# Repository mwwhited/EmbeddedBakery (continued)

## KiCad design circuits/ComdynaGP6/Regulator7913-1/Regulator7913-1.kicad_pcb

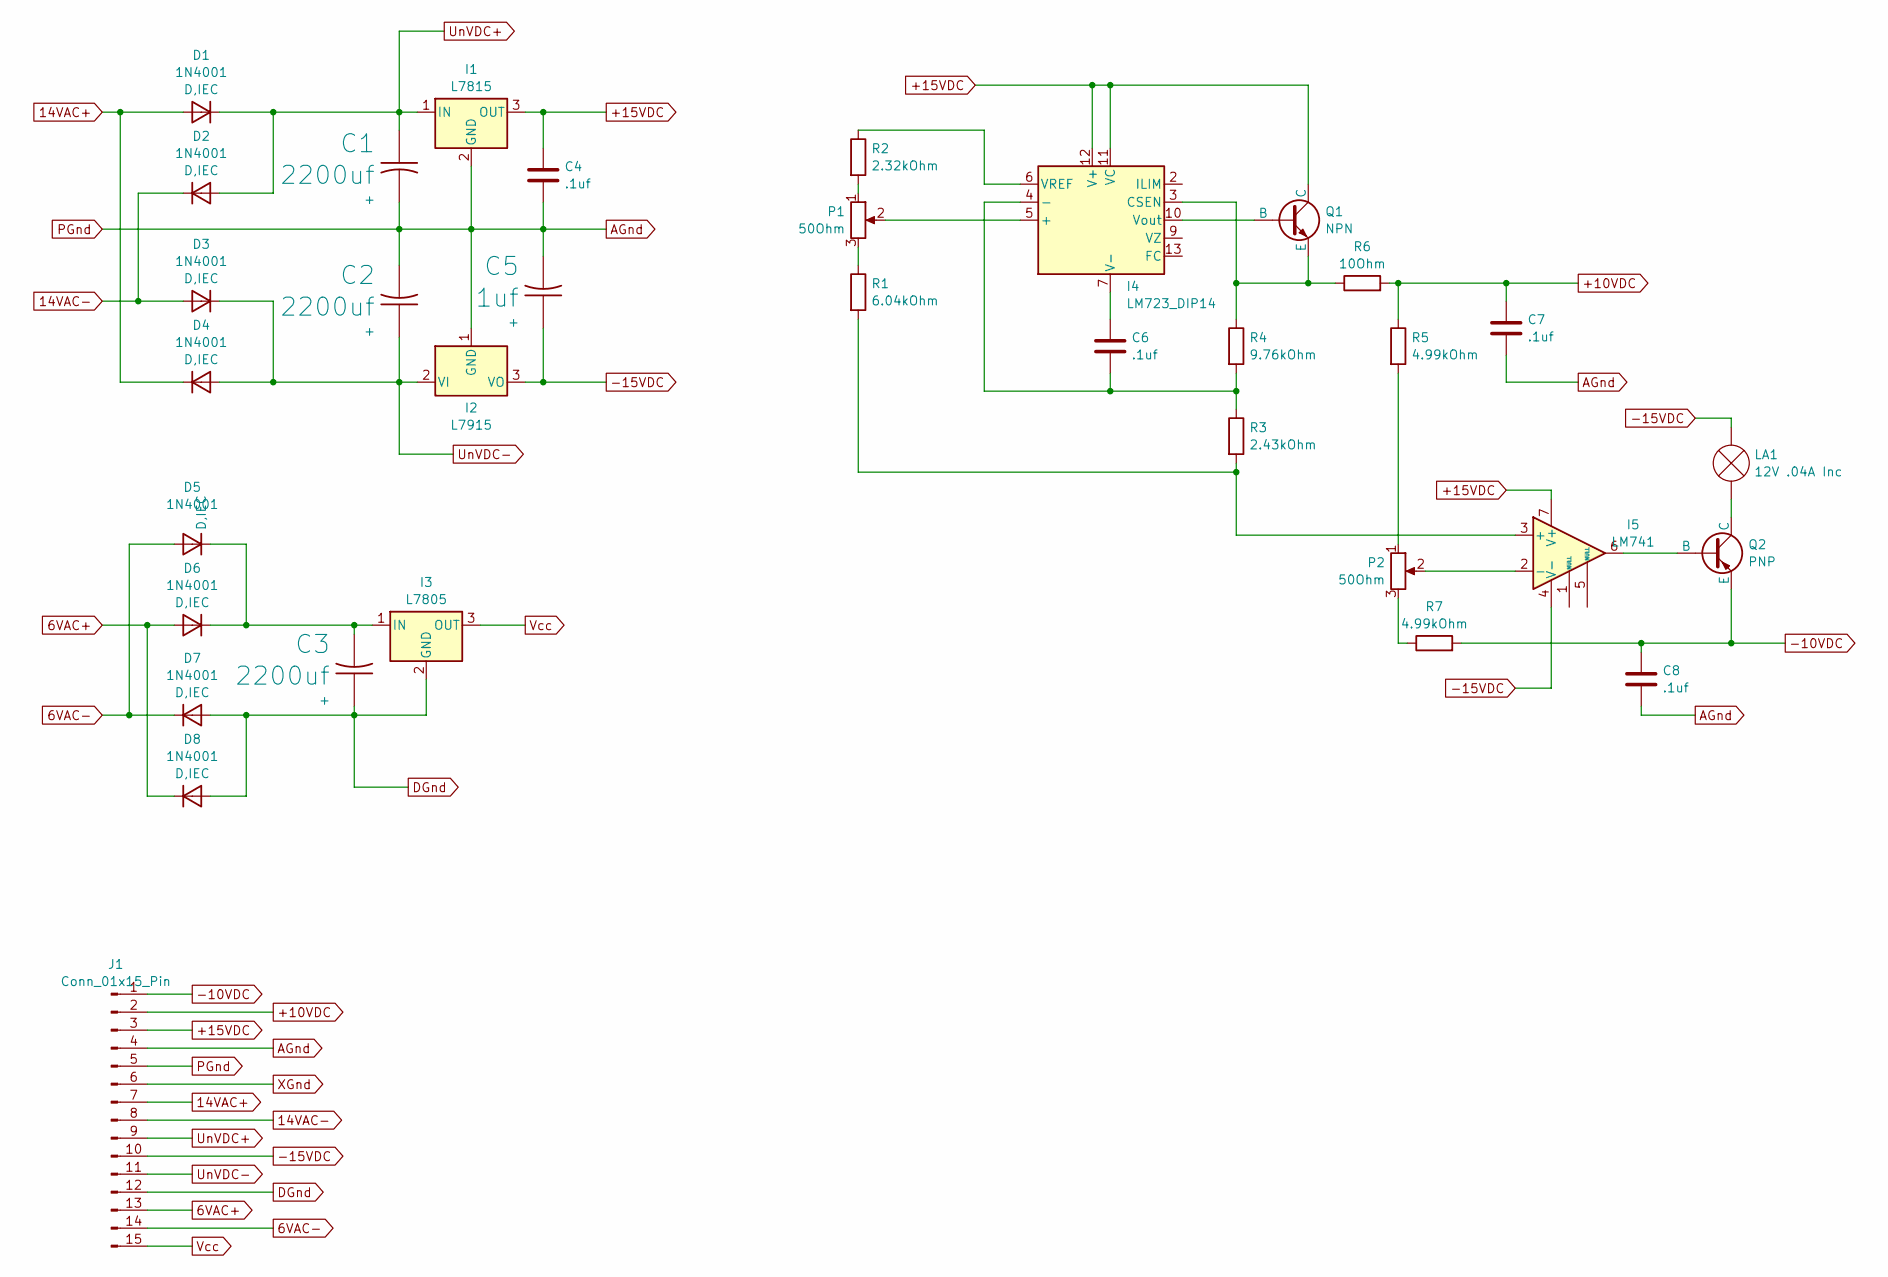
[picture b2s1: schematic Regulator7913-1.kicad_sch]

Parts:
C1, C2, C3: 2200uf; CP_Axial_L30.0mm_D15.0mm_P35.00mm_Horizontal
C4, C6, C7, C8: .1uf; CP_Radial_Tantal_D4.5mm_P5.00mm
C5: 1uf; CP_Radial_Tantal_D4.5mm_P5.00mm
D1, D2, D3, D4, D5, D6, D7, D8: 1N4001; D_5W_P12.70mm_Horizontal
I1: L7815; TO-220-3_Vertical
I2: L7915; TO-220-3_Vertical
I3: L7805; TO-220-3_Vertical
I4: LM723_DIP14; DIP-14_W7.62mm
I5: LM741; DIP-8_W7.62mm_Socket
J1: Conn_01x15_Pin; PinHeader_1x15_P2.54mm_Horizontal
LA1: 12V .04A Inc; PinHeader_1x02_P2.54mm_Horizontal
P1, P2: 50Ohm; Potentiometer_Bourns_3296W_Vertical
Q1: NPN; TO-220-3_Vertical
Q2: PNP; TO-220-3_Vertical
R1: 6.04kOhm; R_Axial_DIN0411_L9.9mm_D3.6mm_P12.70mm_Horizontal
R2: 2.32kOhm; R_Axial_DIN0411_L9.9mm_D3.6mm_P12.70mm_Horizontal
R3: 2.43kOhm; R_Axial_DIN0411_L9.9mm_D3.6mm_P12.70mm_Horizontal
R4: 9.76kOhm; R_Axial_DIN0411_L9.9mm_D3.6mm_P12.70mm_Horizontal
R5, R7: 4.99kOhm; R_Axial_DIN0411_L9.9mm_D3.6mm_P12.70mm_Horizontal
R6: 10Ohm; R_Axial_DIN0411_L9.9mm_D3.6mm_P12.70mm_Horizontal

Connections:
6VAC+: D6.2 (A+), D8.1 (K-), J1.13
6VAC-: D5.2 (A+), D7.1 (K-), J1.14
14VAC+: D1.2 (A+), D4.1 (K-), J1.7
14VAC-: D2.1 (K-), D3.2 (A+), J1.8
+10VDC: C7.1, J1.2, R5.1, R6.2
+15VDC: C4.1, I1.3 (OUT), I4.11 (VC), I4.12 (V+), I5.7 (V+), J1.3, Q1.1 (C)
-10VDC: C8.1, J1.1, Q2.3 (E), R7.2
-15VDC: C5.1 (+), I2.3 (VO), I5.4 (V-), J1.10, LA1.2 (+)
AGnd: C1.2 (-), C2.2 (-), C4.2, C5.2 (-), C7.2, C8.2, I1.2 (GND), I2.1 (GND), J1.4, J1.5
DGnd: C3.1 (+), D7.2 (A+), D8.2 (A+), I3.2 (GND), J1.12
unnamed: C3.2 (-), D5.1 (K-), D6.1 (K-), I3.1 (IN)
unnamed: I4.5 (+), P1.2
unnamed: C6.2, I4.4 (-), R3.1, R4.2
unnamed: I4.3 (CSEN), Q1.3 (E), R4.1, R6.1
unnamed: C6.1, I4.7 (V-)
unnamed: I4.6 (VREF), R2.1
unnamed: I4.10 (Vout), Q1.2 (B)
unnamed: I5.3 (+), R1.2, R3.2
unnamed: I5.2 (-), P2.2
unnamed: LA1.1 (-), Q2.1 (C)
unnamed: P1.1, R2.2
unnamed: P1.3, R1.1
unnamed: P2.1, R5.2
unnamed: P2.3, R7.1
unnamed: I5.6, Q2.2 (B)
UnVDC+: C1.1 (+), D1.1 (K-), D2.2 (A+), I1.1 (IN), J1.9
UnVDC-: C2.1 (+), D3.1 (K-), D4.2 (A+), I2.2 (VI), J1.11
Vcc: I3.3 (OUT), J1.15
XGnd: J1.6

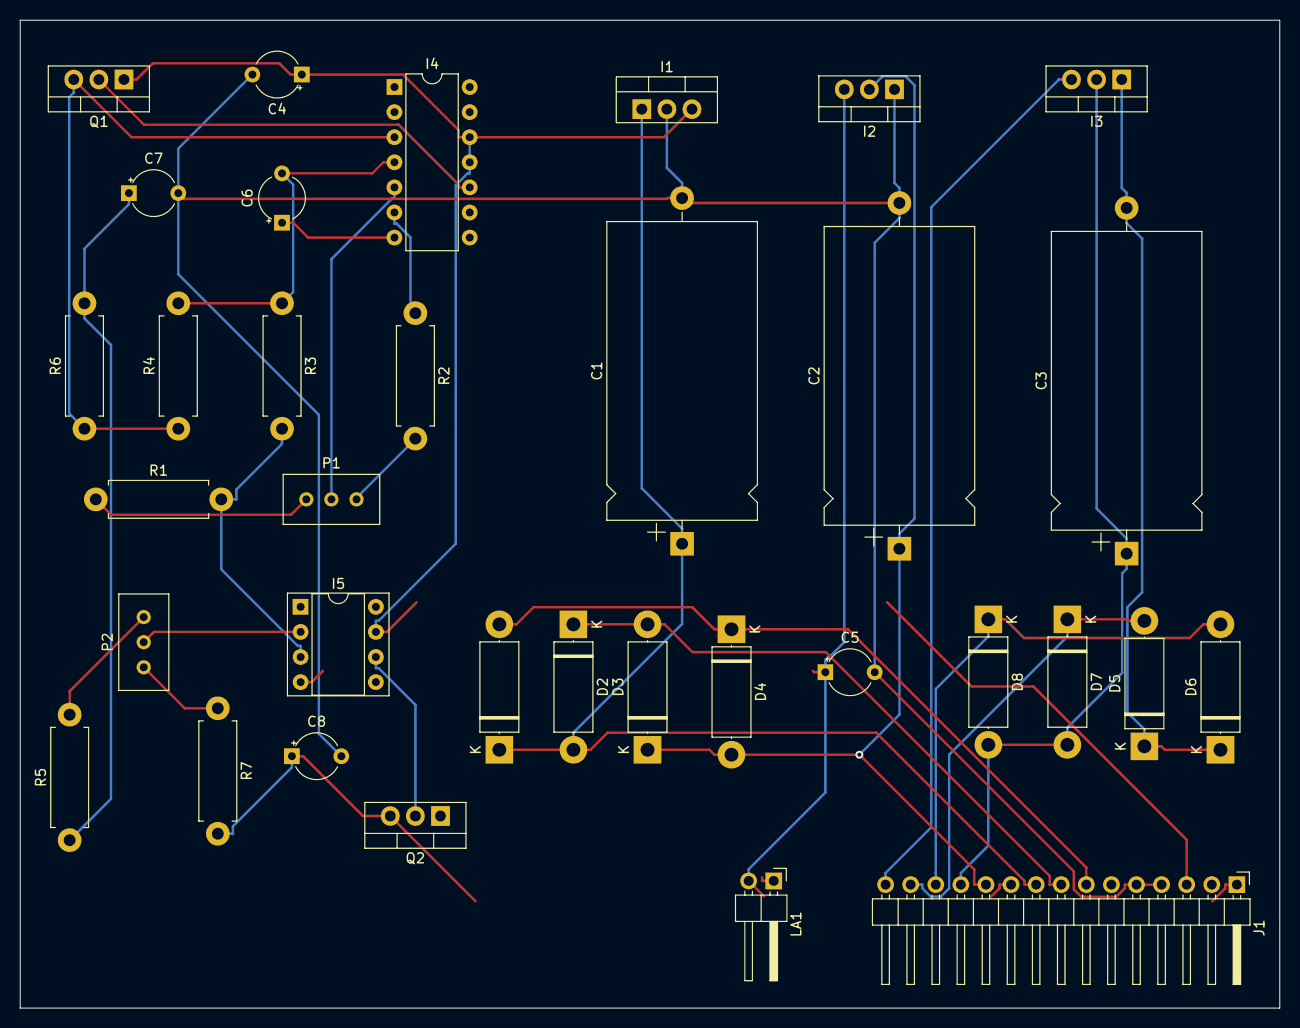
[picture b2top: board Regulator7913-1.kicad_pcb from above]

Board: 2 copper layers, 127.5 x 100.0 mm, 34 parts (0 on the bottom side), 28 nets.

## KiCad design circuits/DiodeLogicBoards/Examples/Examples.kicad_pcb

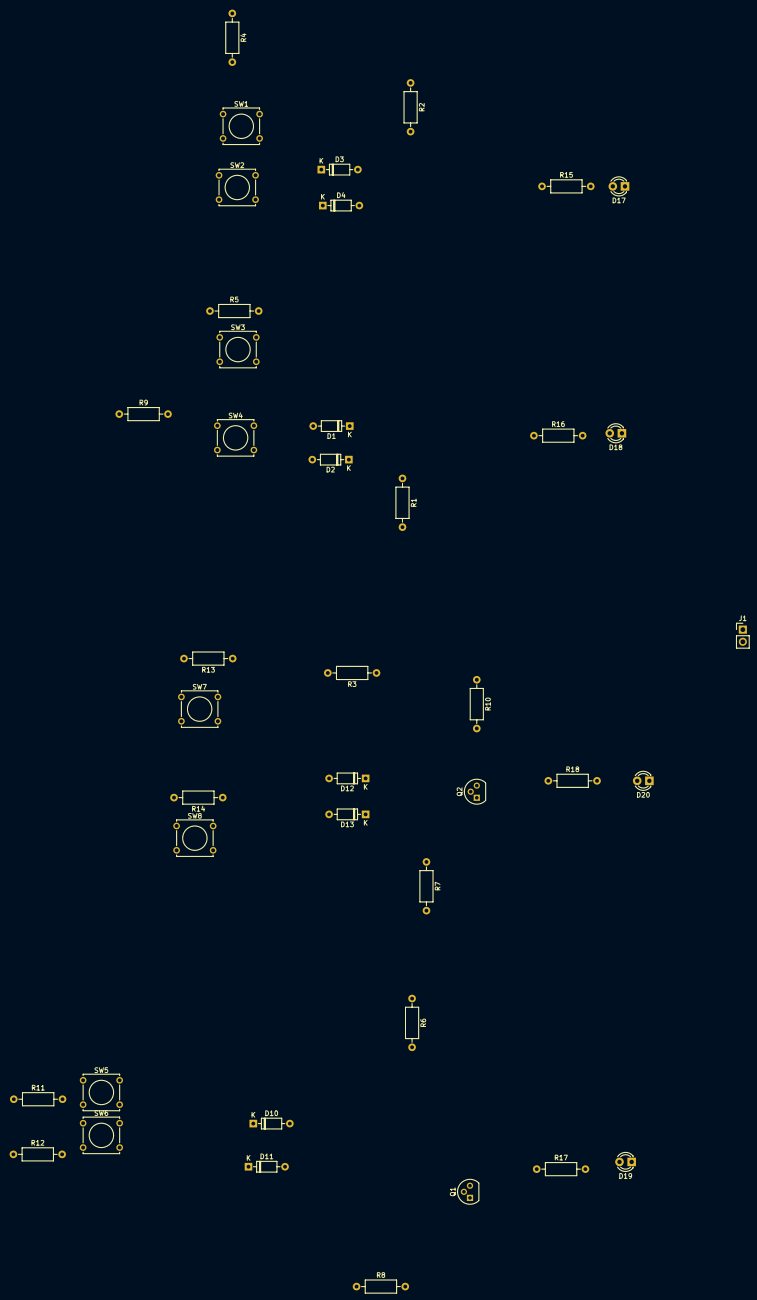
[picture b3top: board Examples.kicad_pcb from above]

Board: 2 copper layers, 41 parts (0 on the bottom side), 20 nets, no tracks yet.

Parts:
D1, D2, D3, D4, D10, D11, D12, D13: 1N4148; D_DO-35_SOD27_P7.62mm_Horizontal
D17, D18, D19, D20: LED; LED_D3.0mm
J1: Conn_01x02_Pin; PinHeader_1x02_P2.54mm_Vertical
Q1, Q2: 2N2222; TO-92
R1, R2, R3, R4, R5, R6, R7, R8, R9, R10, R11, R12, R13, R14: 1k; R_Axial_DIN0207_L6.3mm_D2.5mm_P10.16mm_Horizontal
R15, R16, R17, R18: 220; R_Axial_DIN0207_L6.3mm_D2.5mm_P10.16mm_Horizontal
SW1, SW2, SW3, SW4, SW5, SW6, SW7, SW8: SW_Push; SW_Tactile_Straight_KSA0Axx1LFTR

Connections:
/Diode Logic/AND-Out: D3.2 (A), D4.2 (A), R2.2, R15.1
/Diode Logic/AND-X: D3.1 (K), R4.2, SW1.2
/Diode Logic/AND-Y: D4.1 (K), R3.2, SW2.2
/Diode Logic/OR-Out: D1.1 (K), D2.1 (K), R1.1, R16.1
/Diode Logic/OR-X: D1.2 (A), R5.2, SW3.2
/Diode Logic/OR-Y: D2.2 (A), R9.2, SW4.2
/Diode Transistor Logic/NAND-Out: Q1.3 (C), R8.2, R17.1
/Diode Transistor Logic/NAND-X: D10.1 (K), R11.2, SW5.2
/Diode Transistor Logic/NAND-Y: D11.1 (K), R12.2, SW6.2
/Diode Transistor Logic/NOR-Out: Q2.3 (C), R10.2, R18.1
/Diode Transistor Logic/NOR-X: D12.2 (A), R13.2, SW7.2
/Diode Transistor Logic/NOR-Y: D13.2 (A), R14.2, SW8.2
GND: D17.1 (K), D18.1 (K), D19.1 (K), D20.1 (K), J1.2, Q2.1 (E), R1.2, R7.2, SW1.1, SW2.1, SW3.1, SW4.1, SW5.1, SW6.1, SW7.1, SW8.1
unnamed: D10.2 (A), D11.2 (A), Q1.2 (B), R6.2
unnamed: D12.1 (K), D13.1 (K), Q2.2 (B), R7.1
unnamed: D17.2 (A), R15.2
unnamed: D18.2 (A), R16.2
unnamed: D19.2 (A), R17.2
unnamed: D20.2 (A), R18.2
VCC: J1.1, R2.1, R3.1, R4.1, R5.1, R6.1, R8.1, R9.1, R10.1, R11.1, R12.1, R13.1, R14.1

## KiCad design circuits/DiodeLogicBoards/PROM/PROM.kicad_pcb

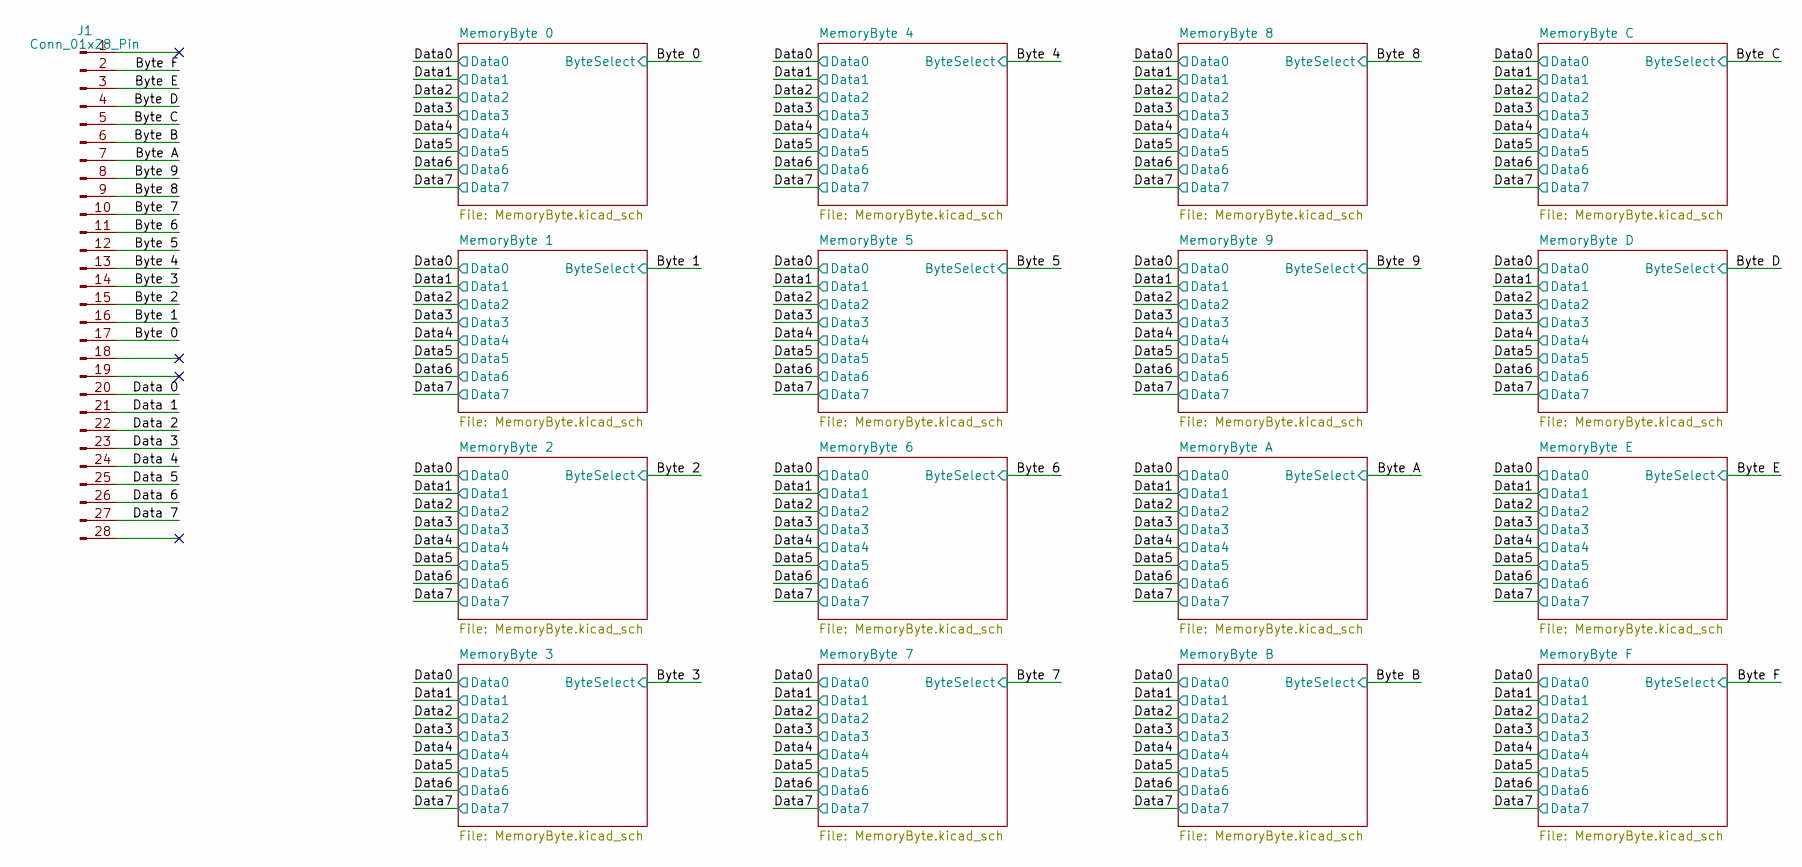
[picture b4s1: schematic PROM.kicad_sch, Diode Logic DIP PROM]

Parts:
J1: Conn_01x28_Pin

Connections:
/Byte 0: J1.17; also elsewhere on the board
/Byte 1: J1.16; also elsewhere on the board
/Byte 2: J1.15; also elsewhere on the board
/Byte 3: J1.14; also elsewhere on the board
/Byte 4: J1.13; also elsewhere on the board
/Byte 5: J1.12; also elsewhere on the board
/Byte 6: J1.11; also elsewhere on the board
/Byte 7: J1.10; also elsewhere on the board
/Byte 8: J1.9; also elsewhere on the board
/Byte 9: J1.8; also elsewhere on the board
/Byte A: J1.7; also elsewhere on the board
/Byte B: J1.6; also elsewhere on the board
/Byte C: J1.5; also elsewhere on the board
/Byte D: J1.4; also elsewhere on the board
/Byte E: J1.3; also elsewhere on the board
/Byte F: J1.2; also elsewhere on the board
/Data 0: J1.19
/Data 1: J1.20
/Data 2: J1.21
/Data 3: J1.22
/Data 4: J1.23
/Data 5: J1.24
/Data 6: J1.25
/Data 7: J1.26

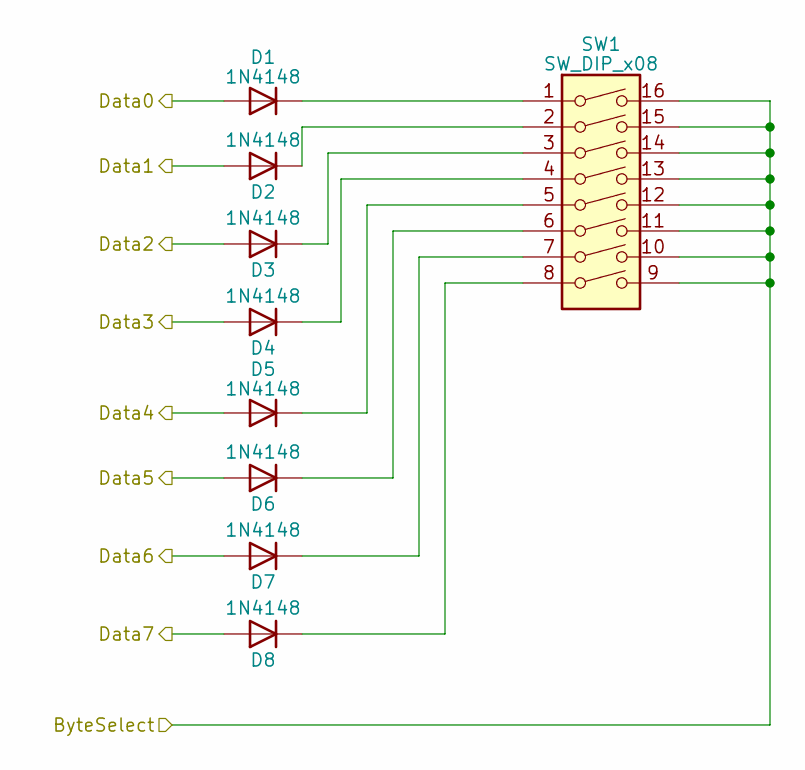
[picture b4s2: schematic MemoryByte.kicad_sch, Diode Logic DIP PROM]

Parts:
D1, D2, D3, D4, D5, D6, D7, D8: 1N4148; D_DO-35_SOD27_P7.62mm_Horizontal
SW1: SW_DIP_x08; DIP-16_W7.62mm

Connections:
/Byte 0: SW1.9, SW1.10, SW1.11, SW1.12, SW1.13, SW1.14, SW1.15, SW1.16; also elsewhere on the board
/Data0: D1.2 (A); also elsewhere on the board
/Data1: D2.2 (A); also elsewhere on the board
/Data2: D3.2 (A); also elsewhere on the board
/Data3: D4.2 (A); also elsewhere on the board
/Data4: D5.2 (A); also elsewhere on the board
/Data5: D6.2 (A); also elsewhere on the board
/Data6: D7.2 (A); also elsewhere on the board
/Data7: D8.2 (A); also elsewhere on the board
unnamed: D1.1 (K), SW1.1
unnamed: D2.1 (K), SW1.2
unnamed: D3.1 (K), SW1.3
unnamed: D4.1 (K), SW1.4
unnamed: D5.1 (K), SW1.5
unnamed: D6.1 (K), SW1.6
unnamed: D7.1 (K), SW1.7
unnamed: D8.1 (K), SW1.8

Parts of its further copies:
D9, D10, D11, D12, D13, D14, D15, D16, D17, D18, D19, D20, D21, D22, D23, D24, D25, D26, D27, D28, D29, D30, D31, D32, D33, D34, D35, D36, D37, D38, D39, D40, D41, D42, D43, D44, D45, D46, D47, D48, D49, D50, D51, D52, D53, D54, D55, D56, D57, D58, D59, D60, D61, D62, D63, D64, D65, D66, D67, D68, D69, D70, D71, D72, D73, D74, D75, D76, D77, D78, D79, D80, D81, D82, D83, D84, D85, D86, D87, D88, D89, D90, D91, D92, D93, D94, D95, D96, D97, D98, D99, D100, D101, D102, D103, D104, D105, D106, D107, D108, D109, D110, D111, D112, D113, D114, D115, D116, D117, D118, D119, D120, D121, D122, D123, D124, D125, D126, D127, D128: 1N4148; D_DO-35_SOD27_P7.62mm_Horizontal
SW2, SW3, SW4, SW5, SW6, SW7, SW8, SW9, SW10, SW11, SW12, SW13, SW14, SW15, SW16: SW_DIP_x08; DIP-16_W7.62mm

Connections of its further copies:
/Byte 1: SW2.9, SW2.10, SW2.11, SW2.12, SW2.13, SW2.14, SW2.15, SW2.16; also elsewhere on the board
/Byte 2: SW3.9, SW3.10, SW3.11, SW3.12, SW3.13, SW3.14, SW3.15, SW3.16; also elsewhere on the board
/Byte 3: SW4.9, SW4.10, SW4.11, SW4.12, SW4.13, SW4.14, SW4.15, SW4.16; also elsewhere on the board
/Byte 4: SW5.9, SW5.10, SW5.11, SW5.12, SW5.13, SW5.14, SW5.15, SW5.16; also elsewhere on the board
/Byte 5: SW6.9, SW6.10, SW6.11, SW6.12, SW6.13, SW6.14, SW6.15, SW6.16; also elsewhere on the board
/Byte 6: SW7.9, SW7.10, SW7.11, SW7.12, SW7.13, SW7.14, SW7.15, SW7.16; also elsewhere on the board
/Byte 7: SW8.9, SW8.10, SW8.11, SW8.12, SW8.13, SW8.14, SW8.15, SW8.16; also elsewhere on the board
/Byte 8: SW9.9, SW9.10, SW9.11, SW9.12, SW9.13, SW9.14, SW9.15, SW9.16; also elsewhere on the board
/Byte 9: SW10.9, SW10.10, SW10.11, SW10.12, SW10.13, SW10.14, SW10.15, SW10.16; also elsewhere on the board
/Byte A: SW11.9, SW11.10, SW11.11, SW11.12, SW11.13, SW11.14, SW11.15, SW11.16; also elsewhere on the board
/Byte B: SW12.9, SW12.10, SW12.11, SW12.12, SW12.13, SW12.14, SW12.15, SW12.16; also elsewhere on the board
/Byte C: SW13.9, SW13.10, SW13.11, SW13.12, SW13.13, SW13.14, SW13.15, SW13.16; also elsewhere on the board
/Byte D: SW14.9, SW14.10, SW14.11, SW14.12, SW14.13, SW14.14, SW14.15, SW14.16; also elsewhere on the board
/Byte E: SW15.9, SW15.10, SW15.11, SW15.12, SW15.13, SW15.14, SW15.15, SW15.16; also elsewhere on the board
/Byte F: SW16.9, SW16.10, SW16.11, SW16.12, SW16.13, SW16.14, SW16.15, SW16.16; also elsewhere on the board
/Data0: D9.2 (A), D17.2 (A), D25.2 (A), D33.2 (A), D41.2 (A), D49.2 (A), D57.2 (A), D65.2 (A), D73.2 (A), D81.2 (A), D89.2 (A), D97.2 (A), D105.2 (A), D113.2 (A), D121.2 (A); also elsewhere on the board
/Data1: D10.2 (A), D18.2 (A), D26.2 (A), D34.2 (A), D42.2 (A), D50.2 (A), D58.2 (A), D66.2 (A), D74.2 (A), D82.2 (A), D90.2 (A), D98.2 (A), D106.2 (A), D114.2 (A), D122.2 (A); also elsewhere on the board
/Data2: D11.2 (A), D19.2 (A), D27.2 (A), D35.2 (A), D43.2 (A), D51.2 (A), D59.2 (A), D67.2 (A), D75.2 (A), D83.2 (A), D91.2 (A), D99.2 (A), D107.2 (A), D115.2 (A), D123.2 (A); also elsewhere on the board
/Data3: D12.2 (A), D20.2 (A), D28.2 (A), D36.2 (A), D44.2 (A), D52.2 (A), D60.2 (A), D68.2 (A), D76.2 (A), D84.2 (A), D92.2 (A), D100.2 (A), D108.2 (A), D116.2 (A), D124.2 (A); also elsewhere on the board
/Data4: D13.2 (A), D21.2 (A), D29.2 (A), D37.2 (A), D45.2 (A), D53.2 (A), D61.2 (A), D69.2 (A), D77.2 (A), D85.2 (A), D93.2 (A), D101.2 (A), D109.2 (A), D117.2 (A), D125.2 (A); also elsewhere on the board
/Data5: D14.2 (A), D22.2 (A), D30.2 (A), D38.2 (A), D46.2 (A), D54.2 (A), D62.2 (A), D70.2 (A), D78.2 (A), D86.2 (A), D94.2 (A), D102.2 (A), D110.2 (A), D118.2 (A), D126.2 (A); also elsewhere on the board
/Data6: D15.2 (A), D23.2 (A), D31.2 (A), D39.2 (A), D47.2 (A), D55.2 (A), D63.2 (A), D71.2 (A), D79.2 (A), D87.2 (A), D95.2 (A), D103.2 (A), D111.2 (A), D119.2 (A), D127.2 (A); also elsewhere on the board
/Data7: D16.2 (A), D24.2 (A), D32.2 (A), D40.2 (A), D48.2 (A), D56.2 (A), D64.2 (A), D72.2 (A), D80.2 (A), D88.2 (A), D96.2 (A), D104.2 (A), D112.2 (A), D120.2 (A), D128.2 (A); also elsewhere on the board
unnamed: D9.1 (K), SW2.1
unnamed: D10.1 (K), SW2.2
unnamed: D11.1 (K), SW2.3
unnamed: D12.1 (K), SW2.4
unnamed: D13.1 (K), SW2.5
unnamed: D14.1 (K), SW2.6
unnamed: D15.1 (K), SW2.7
unnamed: D16.1 (K), SW2.8
unnamed: D17.1 (K), SW3.1
unnamed: D18.1 (K), SW3.2
unnamed: D19.1 (K), SW3.3
unnamed: D20.1 (K), SW3.4
unnamed: D21.1 (K), SW3.5
unnamed: D22.1 (K), SW3.6
unnamed: D23.1 (K), SW3.7
unnamed: D24.1 (K), SW3.8
unnamed: D25.1 (K), SW4.1
unnamed: D26.1 (K), SW4.2
unnamed: D27.1 (K), SW4.3
unnamed: D28.1 (K), SW4.4
unnamed: D29.1 (K), SW4.5
unnamed: D30.1 (K), SW4.6
unnamed: D31.1 (K), SW4.7
unnamed: D32.1 (K), SW4.8
unnamed: D33.1 (K), SW5.1
unnamed: D34.1 (K), SW5.2
unnamed: D35.1 (K), SW5.3
unnamed: D36.1 (K), SW5.4
unnamed: D37.1 (K), SW5.5
unnamed: D38.1 (K), SW5.6
unnamed: D39.1 (K), SW5.7
unnamed: D40.1 (K), SW5.8
unnamed: D41.1 (K), SW6.1
unnamed: D42.1 (K), SW6.2
unnamed: D43.1 (K), SW6.3
unnamed: D44.1 (K), SW6.4
unnamed: D45.1 (K), SW6.5
unnamed: D46.1 (K), SW6.6
unnamed: D47.1 (K), SW6.7
unnamed: D48.1 (K), SW6.8
unnamed: D49.1 (K), SW7.1
unnamed: D50.1 (K), SW7.2
unnamed: D51.1 (K), SW7.3
unnamed: D52.1 (K), SW7.4
unnamed: D53.1 (K), SW7.5
unnamed: D54.1 (K), SW7.6
unnamed: D55.1 (K), SW7.7
unnamed: D56.1 (K), SW7.8
unnamed: D57.1 (K), SW8.1
unnamed: D58.1 (K), SW8.2
unnamed: D59.1 (K), SW8.3
unnamed: D60.1 (K), SW8.4
unnamed: D61.1 (K), SW8.5
unnamed: D62.1 (K), SW8.6
unnamed: D63.1 (K), SW8.7
unnamed: D64.1 (K), SW8.8
unnamed: D65.1 (K), SW9.1
unnamed: D66.1 (K), SW9.2
unnamed: D67.1 (K), SW9.3
unnamed: D68.1 (K), SW9.4
unnamed: D69.1 (K), SW9.5
unnamed: D70.1 (K), SW9.6
unnamed: D71.1 (K), SW9.7
unnamed: D72.1 (K), SW9.8
unnamed: D73.1 (K), SW10.1
unnamed: D74.1 (K), SW10.2
unnamed: D75.1 (K), SW10.3
unnamed: D76.1 (K), SW10.4
unnamed: D77.1 (K), SW10.5
unnamed: D78.1 (K), SW10.6
unnamed: D79.1 (K), SW10.7
unnamed: D80.1 (K), SW10.8
unnamed: D81.1 (K), SW11.1
unnamed: D82.1 (K), SW11.2
unnamed: D83.1 (K), SW11.3
unnamed: D84.1 (K), SW11.4
unnamed: D85.1 (K), SW11.5
unnamed: D86.1 (K), SW11.6
unnamed: D87.1 (K), SW11.7
unnamed: D88.1 (K), SW11.8
unnamed: D89.1 (K), SW12.1
unnamed: D90.1 (K), SW12.2
unnamed: D91.1 (K), SW12.3
unnamed: D92.1 (K), SW12.4
unnamed: D93.1 (K), SW12.5
unnamed: D94.1 (K), SW12.6
unnamed: D95.1 (K), SW12.7
unnamed: D96.1 (K), SW12.8
unnamed: D97.1 (K), SW13.1
unnamed: D98.1 (K), SW13.2
unnamed: D99.1 (K), SW13.3
unnamed: D100.1 (K), SW13.4
unnamed: D101.1 (K), SW13.5
unnamed: D102.1 (K), SW13.6
unnamed: D103.1 (K), SW13.7
unnamed: D104.1 (K), SW13.8
unnamed: D105.1 (K), SW14.1
unnamed: D106.1 (K), SW14.2
unnamed: D107.1 (K), SW14.3
unnamed: D108.1 (K), SW14.4
unnamed: D109.1 (K), SW14.5
unnamed: D110.1 (K), SW14.6
unnamed: D111.1 (K), SW14.7
unnamed: D112.1 (K), SW14.8
unnamed: D113.1 (K), SW15.1
unnamed: D114.1 (K), SW15.2
unnamed: D115.1 (K), SW15.3
unnamed: D116.1 (K), SW15.4
unnamed: D117.1 (K), SW15.5
unnamed: D118.1 (K), SW15.6
unnamed: D119.1 (K), SW15.7
unnamed: D120.1 (K), SW15.8
unnamed: D121.1 (K), SW16.1
unnamed: D122.1 (K), SW16.2
unnamed: D123.1 (K), SW16.3
unnamed: D124.1 (K), SW16.4
unnamed: D125.1 (K), SW16.5
unnamed: D126.1 (K), SW16.6
unnamed: D127.1 (K), SW16.7
unnamed: D128.1 (K), SW16.8

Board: 2 copper layers, 145 parts (0 on the bottom side), 152 nets, no tracks yet.

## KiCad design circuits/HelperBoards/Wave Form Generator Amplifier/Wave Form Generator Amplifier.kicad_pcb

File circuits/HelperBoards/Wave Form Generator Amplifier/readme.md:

# Wave Form Amplifier

By: Matthew Whited
Out-of-Band Development 2023

## Summary

This is a schematic for a LM324 based amplifier that takes provides matching amplification/attenuation and DC offset to an arbitray wave form generator.

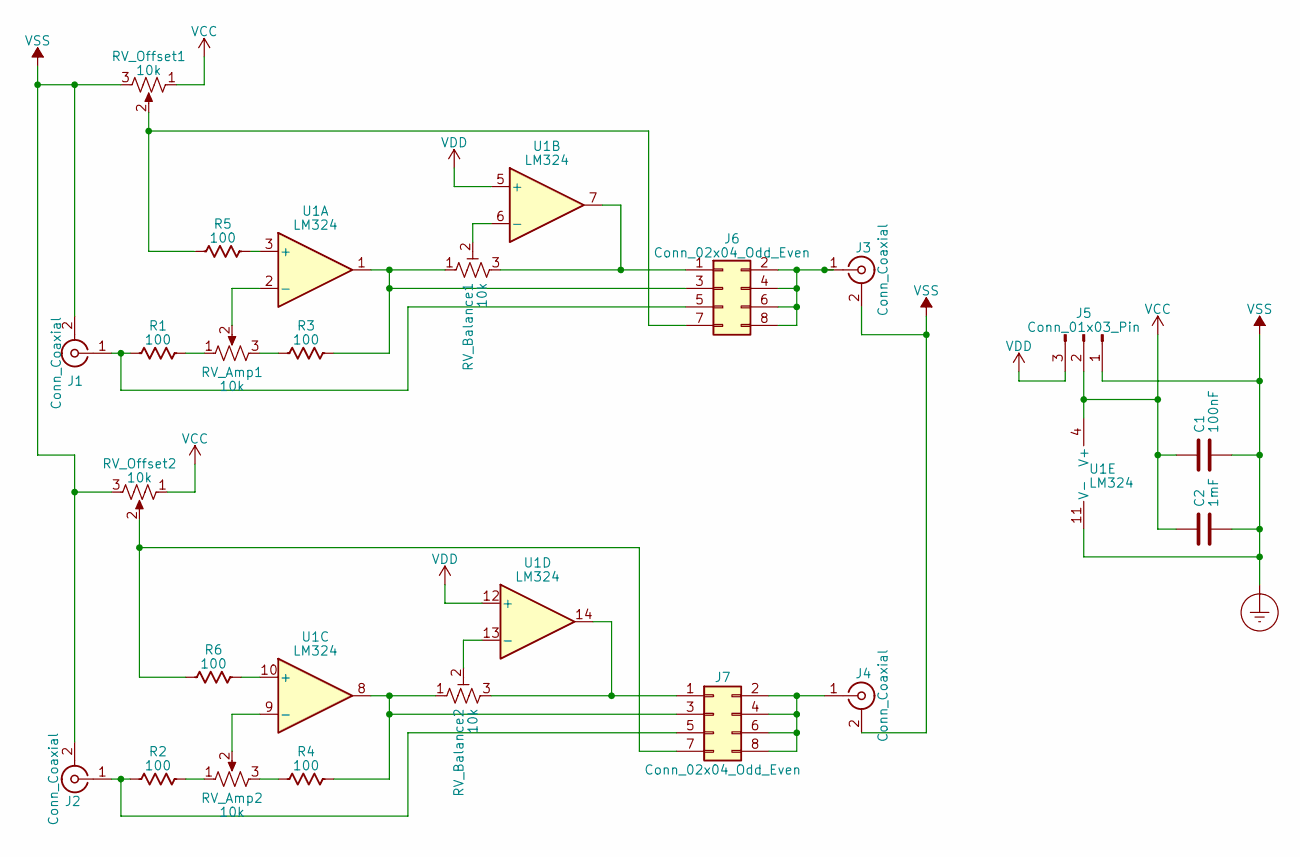
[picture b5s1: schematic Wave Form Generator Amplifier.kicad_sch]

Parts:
C1: 100nF; C_Rect_L4.0mm_W2.5mm_P2.50mm
C2: 1mF; CP_Radial_D5.0mm_P2.50mm
J1, J2, J3, J4: Conn_Coaxial; BNC_Amphenol_B6252HB-NPP3G-50_Horizontal
J5: Conn_01x03_Pin; PinHeader_1x03_P2.54mm_Vertical
J6, J7: Conn_02x04_Odd_Even; PinHeader_2x04_P2.54mm_Vertical
R1, R2, R3, R4, R5, R6: 100; R_Axial_DIN0207_L6.3mm_D2.5mm_P10.16mm_Horizontal
RV_Amp1, RV_Amp2: 10k; JST_XH_B3B-XH-AM_1x03_P2.50mm_Vertical
RV_Balance1, RV_Balance2: 10k; Potentiometer_Bourns_3296W_Vertical
RV_Offset1, RV_Offset2: 10k; JST_XH_B3B-XH-AM_1x03_P2.50mm_Vertical
U1: LM324; DIP-14_W7.62mm_Socket

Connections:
Earth_Protective: C1.2, C2.2, J1.2 (Ext), J2.2 (Ext), J3.2 (Ext), J4.2 (Ext), J5.1, RV_Offset1.3, RV_Offset2.3, U1.11 (V-)
unnamed: J1.1 (In), J6.5, R1.1
unnamed: J2.1 (In), J7.5, R2.1
unnamed: J3.1 (In), J6.2, J6.4, J6.6, J6.8
unnamed: J4.1 (In), J7.2, J7.4, J7.6, J7.8
unnamed: J6.1, RV_Balance1.3, U1.7
unnamed: J6.3, R3.2, RV_Balance1.1, U1.1
unnamed: J6.7, R5.1, RV_Offset1.2
unnamed: J7.1, RV_Balance2.3, U1.14
unnamed: J7.3, R4.2, RV_Balance2.1, U1.8
unnamed: J7.7, R6.1, RV_Offset2.2
unnamed: R1.2, RV_Amp1.1
unnamed: R2.2, RV_Amp2.1
unnamed: R3.1, RV_Amp1.3
unnamed: R4.1, RV_Amp2.3
unnamed: R5.2, U1.3 (+)
unnamed: RV_Amp1.2, U1.2 (-)
unnamed: RV_Balance1.2, U1.6 (-)
unnamed: R6.2, U1.10 (+)
unnamed: RV_Amp2.2, U1.9 (-)
unnamed: RV_Balance2.2, U1.13 (-)
VCC: C1.1, C2.1, J5.2, RV_Offset1.1, RV_Offset2.1, U1.4 (V+)
VDD: J5.3, U1.5 (+), U1.12 (+)

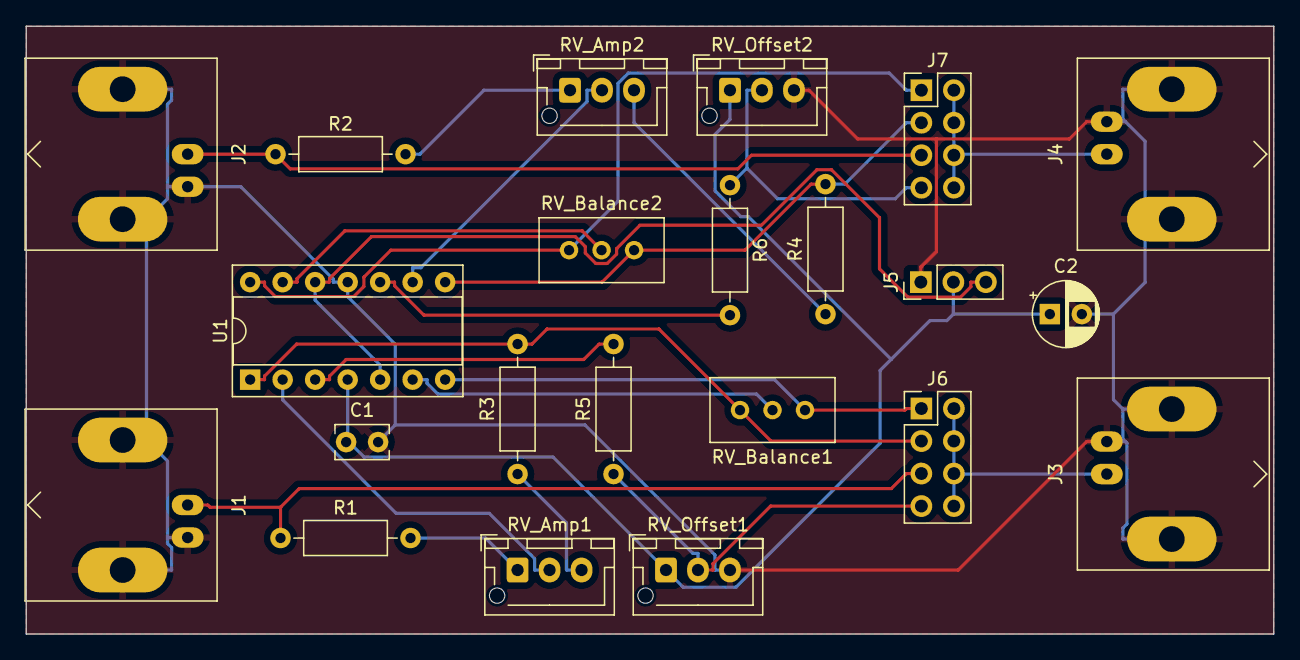
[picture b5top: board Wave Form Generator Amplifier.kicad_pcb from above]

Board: 2 copper layers, 97.5 x 47.5 mm, 22 parts (0 on the bottom side), 23 nets.

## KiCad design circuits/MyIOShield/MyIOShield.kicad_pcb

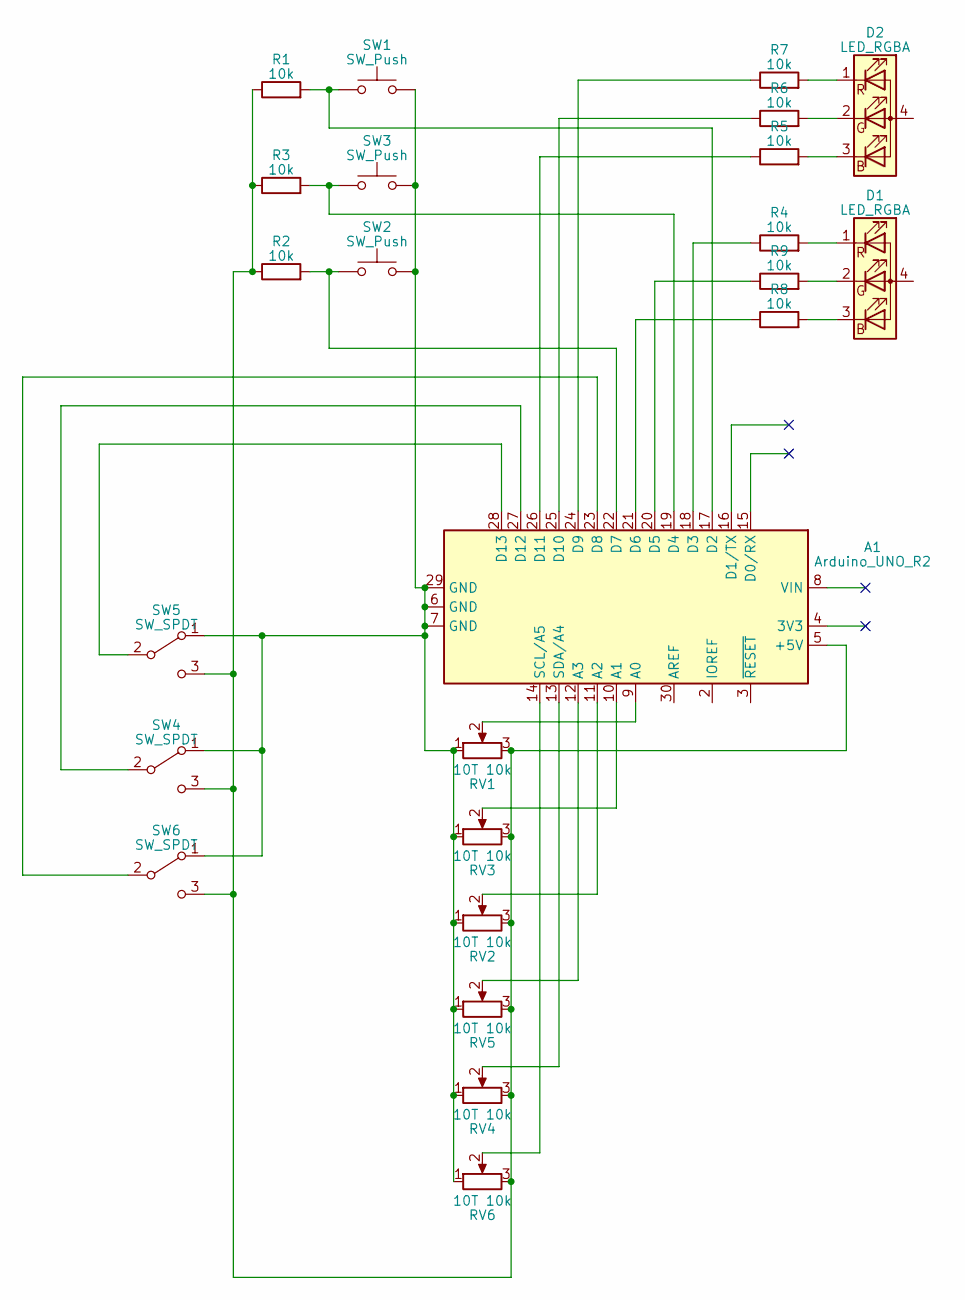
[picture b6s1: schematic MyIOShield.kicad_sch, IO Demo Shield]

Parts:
A1: Arduino_UNO_R2
D1, D2: LED_RGBA; LED_D5.0mm-4_RGB
R1, R2, R3, R4, R5, R6, R7, R8, R9: 10k; R_Axial_DIN0207_L6.3mm_D2.5mm_P7.62mm_Horizontal
RV1, RV2, RV3, RV4, RV5, RV6: 10T 10k; Potentiometer_Bourns_3296W_Vertical
SW1, SW2, SW3: SW_Push; SW_Tactile_Straight_KSA0Axx1LFTR
SW4, SW5, SW6: SW_SPDT; SW_CuK_OS102011MA1QN1_SPDT_Angled

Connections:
unnamed: A1.5 (+5V), R1.1, R2.1, R3.1, RV1.3, RV2.3, RV3.3, RV4.3, RV5.3, RV6.3, SW4.3 (C), SW5.3 (C), SW6.3 (C)
unnamed: A1.9 (A0), RV1.2
unnamed: A1.10 (A1), RV3.2
unnamed: A1.11 (A2), RV2.2
unnamed: A1.12 (A3), RV5.2
unnamed: A1.17 (D2), R1.2, SW1.1
unnamed: A1.18 (D3), R4.1
unnamed: A1.19 (D4), R3.2, SW3.1
unnamed: A1.20 (D5), R9.1
unnamed: A1.21 (D6), R8.1
unnamed: A1.22 (D7), R2.2, SW2.1
unnamed: A1.23 (D8), SW6.2 (B)
unnamed: A1.24 (D9), R7.1
unnamed: A1.25 (D10), R6.1
unnamed: A1.26 (D11), R5.1
unnamed: A1.27 (D12), SW4.2 (B)
unnamed: A1.28 (D13), SW5.2 (B)
unnamed: A1.14 (SCL/A5), RV6.2
unnamed: A1.13 (SDA/A4), RV4.2
unnamed: D2.3 (BK), R5.2
unnamed: D2.2 (GK), R6.2
unnamed: D2.1 (RK), R7.2
unnamed: D1.3 (BK), R8.2
unnamed: D1.2 (GK), R9.2
unnamed: D1.1 (RK), R4.2
unnamed: A1.6 (GND), A1.7 (GND), A1.29 (GND), RV1.1, RV2.1, RV3.1, RV4.1, RV5.1, RV6.1, SW1.2, SW2.2, SW3.2, SW4.1 (A), SW5.1 (A), SW6.1 (A)

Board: 2 copper layers, 24 parts (0 on the bottom side), 26 nets, no tracks yet.

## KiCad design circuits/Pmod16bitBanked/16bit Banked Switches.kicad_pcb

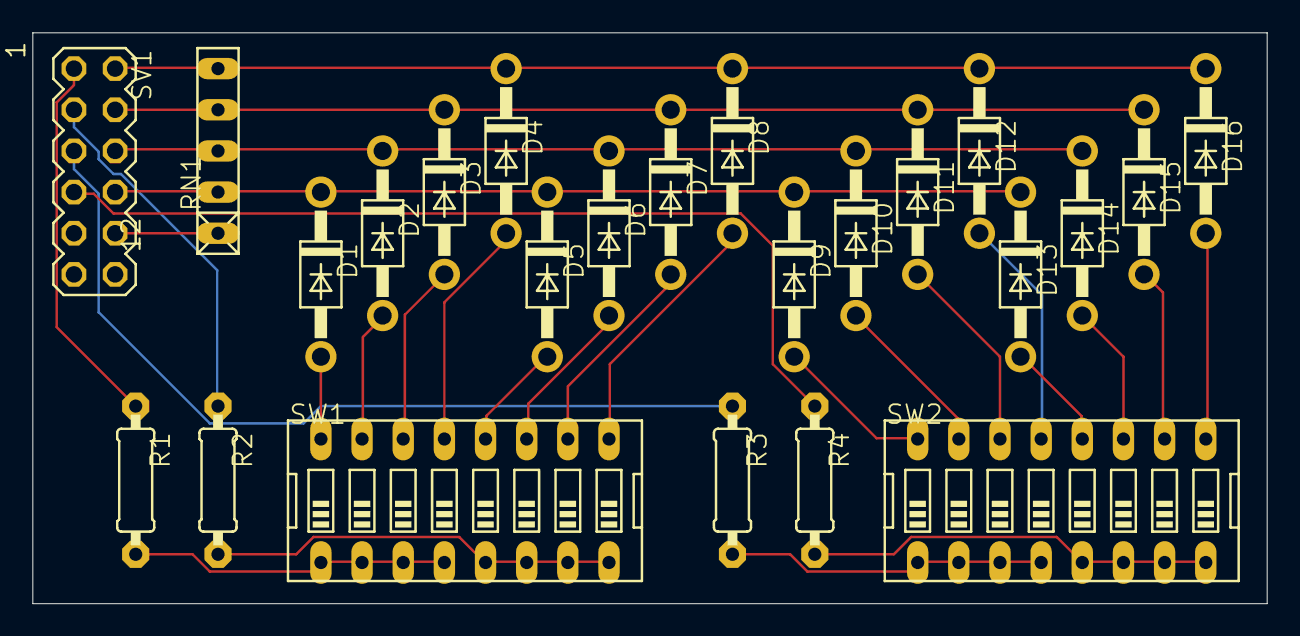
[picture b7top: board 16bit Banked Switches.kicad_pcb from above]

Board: 2 copper layers, 76.2 x 35.2 mm, 24 parts (0 on the bottom side), 29 nets.

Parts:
D1, D2, D3, D4, D5, D6, D7, D8, D9, D10, D11, D12, D13, D14, D15, D16: 1N4004; DO41-10
R1, R2, R3, R4: 0207_9
RN1: RN-5
SV1: MA06-2
SW1, SW2: EDG-08

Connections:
unnamed: R1.2, SW1.1, SW1.2, SW1.3, SW1.4
unnamed: R2.2, SW1.5, SW1.6, SW1.7, SW1.8
unnamed: R3.2, SW2.1, SW2.2, SW2.3, SW2.4
unnamed: R4.2, SW2.5, SW2.6, SW2.7, SW2.8
unnamed: D4.C, D8.C, D12.C, D16.C, RN1.5, SV1.2
unnamed: D1.A, SW1.16
unnamed: D2.A, SW1.15
unnamed: D3.A, SW1.14
unnamed: D4.A, SW1.13
unnamed: D5.A, SW1.12
unnamed: D6.A, SW1.11
unnamed: D7.A, SW1.10
unnamed: D8.A, SW1.9
unnamed: D9.A, SW2.16
unnamed: D10.A, SW2.15
unnamed: D11.A, SW2.14
unnamed: D12.A, SW2.13
unnamed: D13.A, SW2.12
unnamed: D14.A, SW2.11
unnamed: D15.A, SW2.10
unnamed: D16.A, SW2.9
unnamed: D1.C, D5.C, D9.C, D13.C, RN1.2, SV1.8
unnamed: D2.C, D6.C, D10.C, D14.C, RN1.3, SV1.6
unnamed: D3.C, D7.C, D11.C, D15.C, RN1.4, SV1.4
unnamed: R1.1, SV1.1
unnamed: RN1.1, SV1.10
unnamed: R2.1, SV1.3
unnamed: R3.1, SV1.5
unnamed: R4.1, SV1.7
